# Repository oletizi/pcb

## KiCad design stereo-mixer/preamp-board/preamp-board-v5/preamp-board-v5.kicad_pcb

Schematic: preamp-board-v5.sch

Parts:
C1, C2: 100nF; CP_Radial_D5.0mm_P2.50mm
C3, C4: 47pF; C_Rect_L7.2mm_W2.5mm_P5.00mm_FKS2_FKP2_MKS2_MKP2
J1: Conn_01x20; 20-pin-2.54-edge-connector
R1, R2: 22K; R_Axial_DIN0204_L3.6mm_D1.6mm_P7.62mm_Horizontal
R3, R4: 47K; R_Axial_DIN0204_L3.6mm_D1.6mm_P7.62mm_Horizontal
U1: LM833N; DIP-8_W7.62mm_Socket

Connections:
/+15V: C1.1, J1.16, U1.8 (+VCC)
/-15V: C2.2, J1.20, U1.4 (-VEE)
/L_GAIN_TERM_A: J1.8, R2.2
/L_GAIN_WIPER: C3.2, J1.1, J1.3, J1.5, J1.6, U1.1 (OUT_A)
/L_IN: J1.2, R4.2
/R_GAIN_TERM_A: J1.12, R1.2
/R_GAIN_WIPER: C4.2, J1.9, J1.10, J1.11, J1.13, U1.7 (OUT_B)
/R_IN: J1.4, R3.2
GND: C1.2, C2.1, J1.7, J1.14, J1.18, U1.3 (+INA), U1.5 (+INB)
unnamed: C3.1, R2.1, R4.1, U1.2 (-INA)
unnamed: C4.1, R1.1, R3.1, U1.6 (-INB)

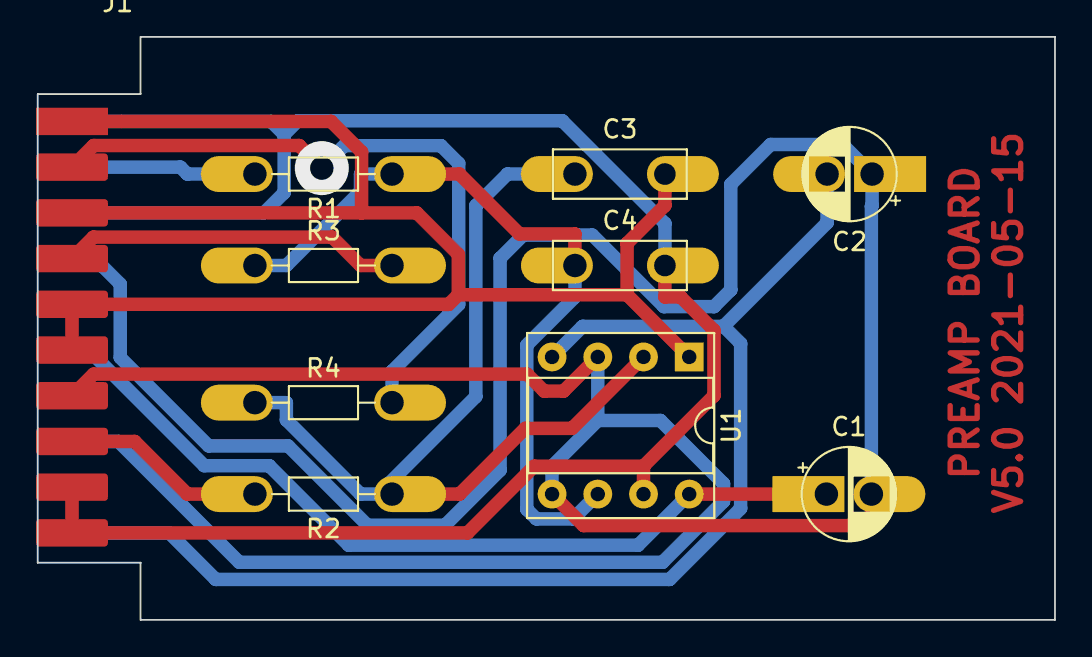
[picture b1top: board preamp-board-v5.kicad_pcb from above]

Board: 2 copper layers, 56.5 x 32.4 mm, 10 parts (0 on the bottom side), 11 nets.

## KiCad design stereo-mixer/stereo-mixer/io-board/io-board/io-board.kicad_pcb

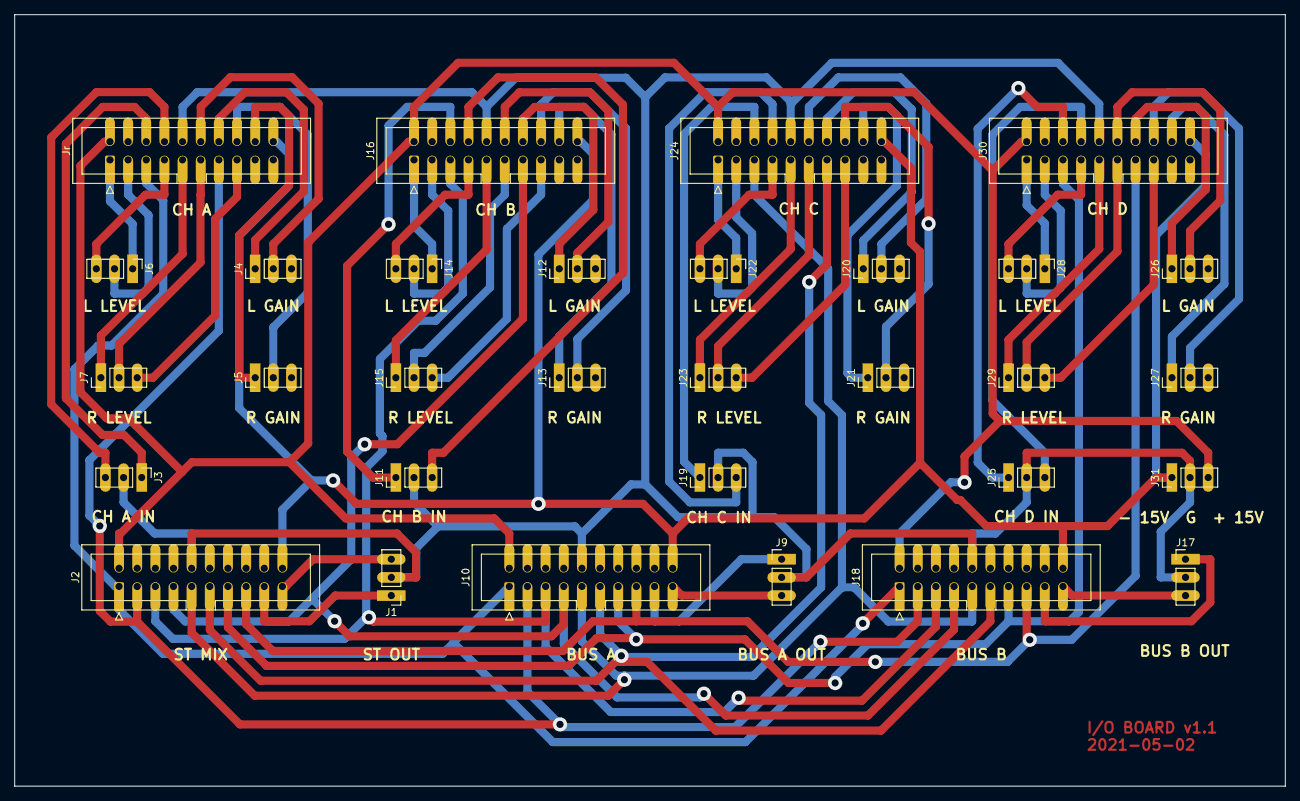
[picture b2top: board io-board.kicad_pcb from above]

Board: 2 copper layers, 177.8 x 108.0 mm, 31 parts (0 on the bottom side), 65 nets.

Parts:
J1: ST OUT; PinHeader_1x03_P2.54mm_Vertical
J2: MIXER BOARD; IDC-Header_2x10_P2.54mm_Vertical
J3: CH A IN: L G R; PinHeader_1x03_P2.54mm_Vertical
J4: CH A L GAIN: TWX; PinHeader_1x03_P2.54mm_Vertical
J5: CH A R GAIN: TWX; PinHeader_1x03_P2.54mm_Vertical
J6: CH A L Level: A W B; PinHeader_1x03_P2.54mm_Vertical
J7: CH A R Level: A W B; PinHeader_1x03_P2.54mm_Vertical
J9: BUS A OUT; PinHeader_1x03_P2.54mm_Vertical
J10: BUS A BOARD; IDC-Header_2x10_P2.54mm_Vertical
J11: CH B IN: L G R; PinHeader_1x03_P2.54mm_Vertical
J12: CH B L GAIN: TWX; PinHeader_1x03_P2.54mm_Vertical
J13: CH B R GAIN: TWX; PinHeader_1x03_P2.54mm_Vertical
J14: CH B L Level: A W B; PinHeader_1x03_P2.54mm_Vertical
J15: CH B R Level: A W B; PinHeader_1x03_P2.54mm_Vertical
J16: CH B PREAMP; IDC-Header_2x10_P2.54mm_Vertical
J17: BUS B OUT; PinHeader_1x03_P2.54mm_Vertical
J18: BUS B BOARD; IDC-Header_2x10_P2.54mm_Vertical
J19: CH C IN: L G R; PinHeader_1x03_P2.54mm_Vertical
J20: CH C L GAIN: TWX; PinHeader_1x03_P2.54mm_Vertical
J21: CH C R GAIN: TWX; PinHeader_1x03_P2.54mm_Vertical
J22: CH C L Level: A W B; PinHeader_1x03_P2.54mm_Vertical
J23: CH C R Level: A W B; PinHeader_1x03_P2.54mm_Vertical
J24: CH C PREAMP; IDC-Header_2x10_P2.54mm_Vertical
J25: CH D IN: L G R; PinHeader_1x03_P2.54mm_Vertical
J26: CH D L GAIN: TWX; PinHeader_1x03_P2.54mm_Vertical
J27: CH D R GAIN: TWX; PinHeader_1x03_P2.54mm_Vertical
J28: CH D L Level: A W B; PinHeader_1x03_P2.54mm_Vertical
J29: CH D R Level: A W B; PinHeader_1x03_P2.54mm_Vertical
J30: CH D PREAMP; IDC-Header_2x10_P2.54mm_Vertical
J31: -15V GND +15V; PinHeader_1x03_P2.54mm_Vertical
Jr: CH A PREAMP; IDC-Header_2x10_P2.54mm_Vertical

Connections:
/+_15V: J2.2, J10.2, J16.2, J18.2, J24.2, J30.2, J31.3, Jr.2
/-_15V: J2.20, J10.20, J16.20, J18.20, J24.20, J30.20, J31.1, Jr.20
/BUS_A_L_OUT: J9.1, J10.17
/BUS_A_R_OUT: J9.3, J10.19
/BUS_B_L_OUT: J17.1, J18.17
/BUS_B_R_OUT: J17.3, J18.19
/CH_A_LEVEL_TERM_B: J6.3, Jr.7
/CH_A_L_GAIN_TERM_A: J4.1, Jr.14
/CH_A_L_GAIN_WIPER: J4.2, Jr.12
/CH_A_L_IN: J3.1, Jr.6
/CH_A_L_LEVEL_TERM_A: J6.1, Jr.1
/CH_A_L_LEVEL_WIPER: J6.2, Jr.3
/CH_A_L_OUT: J2.1, J10.1, J18.1, Jr.5
/CH_A_R_GAIN_TERM_A: J5.1, Jr.18
/CH_A_R_GAIN_WIPER: J5.2, Jr.16
/CH_A_R_IN: J3.3, Jr.8
/CH_A_R_LEVEL_TERM_A: J7.1, Jr.9
/CH_A_R_LEVEL_TERM_B: J7.3, Jr.15
/CH_A_R_LEVEL_WIPER: J7.2, Jr.11
/CH_A_R_OUT: J2.3, J10.3, J18.3, Jr.13
/CH_B_LEVEL_TERM_B: J14.3, J16.7
/CH_B_L_GAIN_TERM_A: J12.1, J16.14
/CH_B_L_GAIN_WIPER: J12.2, J16.12
/CH_B_L_IN: J11.1, J16.6
/CH_B_L_LEVEL_TERM_A: J14.1, J16.1
/CH_B_L_LEVEL_WIPER: J14.2, J16.3
/CH_B_L_OUT: J2.5, J10.5, J16.5, J18.5
/CH_B_R_GAIN_TERM_A: J13.1, J16.18
/CH_B_R_GAIN_WIPER: J13.2, J16.16
/CH_B_R_IN: J11.3, J16.8
/CH_B_R_LEVEL_TERM_A: J15.1, J16.9
/CH_B_R_LEVEL_TERM_B: J15.3, J16.15
/CH_B_R_LEVEL_WIPER: J15.2, J16.11
/CH_B_R_OUT: J2.7, J10.7, J16.13, J18.7
/CH_C_LEVEL_TERM_B: J22.3, J24.7
/CH_C_L_GAIN_TERM_A: J20.1, J24.14
/CH_C_L_GAIN_WIPER: J20.2, J24.12
/CH_C_L_IN: J19.1, J24.6
/CH_C_L_LEVEL_TERM_A: J22.1, J24.1
/CH_C_L_LEVEL_WIPER: J22.2, J24.3
/CH_C_L_OUT: J2.9, J10.9, J18.9, J24.5
/CH_C_R_GAIN_TERM_A: J21.1, J24.18
/CH_C_R_GAIN_WIPER: J21.2, J24.16
/CH_C_R_IN: J19.3, J24.8
/CH_C_R_LEVEL_TERM_A: J23.1, J24.9
/CH_C_R_LEVEL_TERM_B: J23.3, J24.15
/CH_C_R_LEVEL_WIPER: J23.2, J24.11
/CH_C_R_OUT: J2.11, J10.11, J18.11, J24.13
/CH_D_LEVEL_TERM_B: J28.3, J30.7
/CH_D_L_GAIN_TERM_A: J26.1, J30.14
/CH_D_L_GAIN_WIPER: J26.2, J30.12
/CH_D_L_IN: J25.1, J30.6
/CH_D_L_LEVEL_TERM_A: J28.1, J30.1
/CH_D_L_LEVEL_WIPER: J28.2, J30.3
/CH_D_L_OUT: J2.13, J10.13, J18.13, J30.5
/CH_D_R_GAIN_TERM_A: J27.1, J30.18
/CH_D_R_GAIN_WIPER: J27.2, J30.16
/CH_D_R_IN: J25.3, J30.8
/CH_D_R_LEVEL_TERM_A: J29.1, J30.9
/CH_D_R_LEVEL_TERM_B: J29.3, J30.15
/CH_D_R_LEVEL_WIPER: J29.2, J30.11
/CH_D_R_OUT: J2.15, J10.15, J18.15, J30.13
/ST_L_OUT: J1.1, J2.17
/ST_R_OUT: J1.3, J2.19
GND: J1.2, J2.10, J3.2, J9.2, J10.10, J11.2, J16.10, J17.2, J18.10, J19.2, J24.10, J25.2, J30.10, J31.2, Jr.10

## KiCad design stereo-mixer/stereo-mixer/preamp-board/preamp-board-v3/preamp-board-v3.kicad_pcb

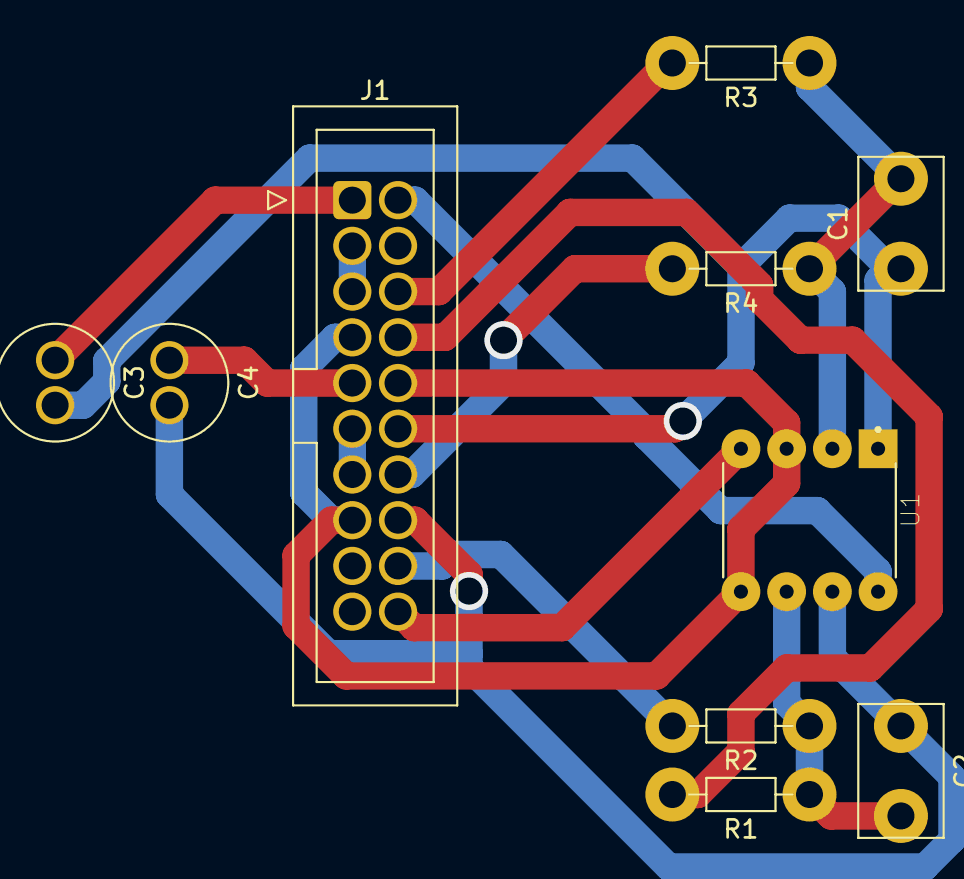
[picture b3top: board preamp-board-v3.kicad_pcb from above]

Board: 2 copper layers, 10 parts (0 on the bottom side), 15 nets.

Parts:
C1, C2: 47pF; C_Rect_L7.2mm_W4.5mm_P5.00mm_FKS2_FKP2_MKS2_MKP2
C3, C4: 100uF; C_Radial_D6.3mm_H11.0mm_P2.50mm
J1: I/O; IDC-Header_2x10_P2.54mm_Vertical
R1, R3: 47K; R_Axial_DIN0204_L3.6mm_D1.6mm_P7.62mm_Horizontal
R2, R4: 22K; R_Axial_DIN0204_L3.6mm_D1.6mm_P7.62mm_Horizontal
U1: LM833N; DIP794W45P254L959H508Q8

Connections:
GND: J1.7, J1.10, J1.15, U1.3, U1.5
unnamed: C1.1, C3.2, J1.12, U1.1
unnamed: C1.2, R3.1, R4.1, U1.2
unnamed: C2.1, C4.2, J1.16, U1.7
unnamed: C2.2, R1.1, R2.1, U1.6
unnamed: C3.1, J1.1
unnamed: C4.1, J1.9
unnamed: J1.2, U1.8
unnamed: J1.3, J1.5
unnamed: J1.6, R3.2
unnamed: J1.8, R1.2
unnamed: J1.11, J1.13
unnamed: J1.14, R4.2
unnamed: J1.18, R2.2
unnamed: J1.20, U1.4

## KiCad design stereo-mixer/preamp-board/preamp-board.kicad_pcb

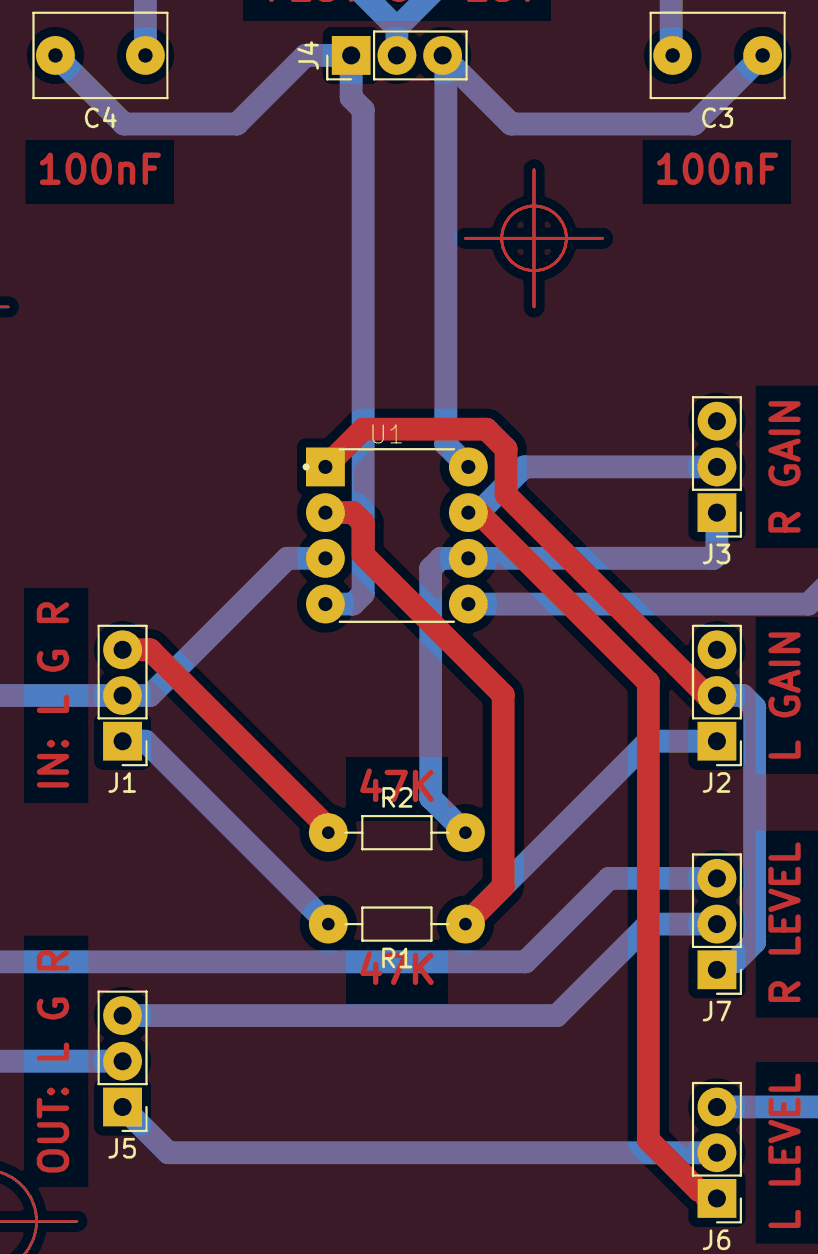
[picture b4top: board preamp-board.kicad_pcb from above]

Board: 2 copper layers, 12 parts (0 on the bottom side), 11 nets.

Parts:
C3, C4: 100nF; C_Rect_L7.2mm_W4.5mm_P5.00mm_FKS2_FKP2_MKS2_MKP2
J1: IN: L G R; PinHeader_1x03_P2.54mm_Vertical
J2: L GAIN POT; PinHeader_1x03_P2.54mm_Vertical
J3: R GAIN POT; PinHeader_1x03_P2.54mm_Vertical
J4: PWR: +15 G -15; PinHeader_1x03_P2.54mm_Vertical
J5: OUT: L G R; PinHeader_1x03_P2.54mm_Vertical
J6: L LEVEL POT; PinHeader_1x03_P2.54mm_Vertical
J7: R LEVEL POT; PinHeader_1x03_P2.54mm_Vertical
R1, R2: 47K; R_Axial_DIN0204_L3.6mm_D1.6mm_P7.62mm_Horizontal
U1: LM833N; DIP794W45P254L959H508Q8

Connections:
GND: C3.2, C4.1, J1.2, J4.2, J5.2, J6.3, J7.3, U1.3, U1.5
unnamed: C3.1, J4.3, U1.8
unnamed: C4.2, J4.1, U1.4
unnamed: J1.1, R1.2
unnamed: J1.3, R2.1
unnamed: J2.1, R1.1, U1.2
unnamed: J2.2, J7.1, U1.1
unnamed: J3.1, R2.2, U1.6
unnamed: J3.2, J6.1, U1.7
unnamed: J5.1, J6.2
unnamed: J5.3, J7.2

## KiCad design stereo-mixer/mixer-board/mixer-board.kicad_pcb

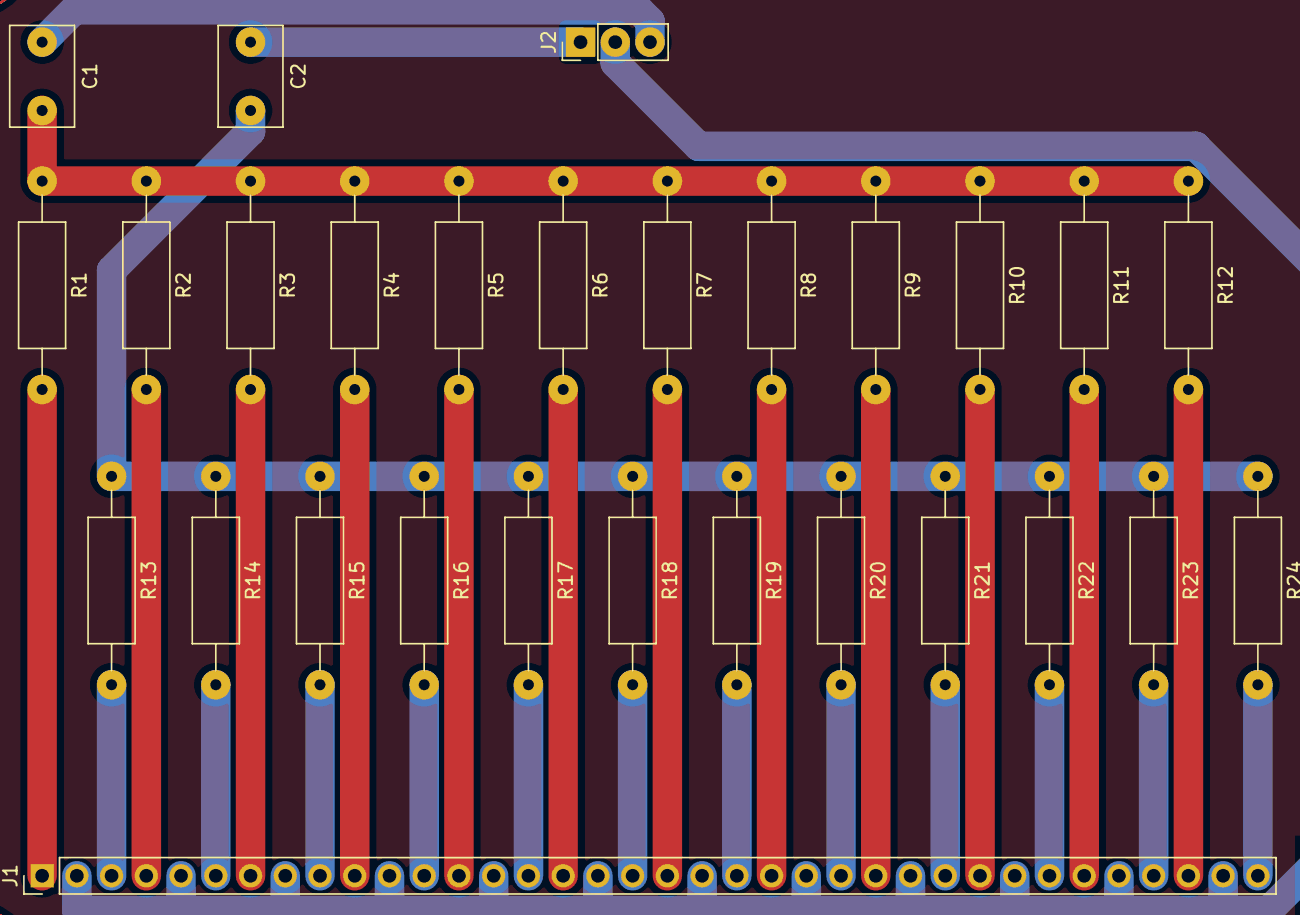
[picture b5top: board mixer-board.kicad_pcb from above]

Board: 2 copper layers, 28 parts (0 on the bottom side), 29 nets.

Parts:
C1, C2: 10uF; C_Rect_L7.2mm_W4.5mm_P5.00mm_FKS2_FKP2_MKS2_MKP2
J1: Conn_01x36_Male; PinHeader_1x36_P2.54mm_Vertical
J2: Conn_01x03_Male; PinHeader_1x03_P2.54mm_Vertical
R1, R2, R3, R4, R5, R6, R7, R8, R9, R10, R11, R12, R13, R14, R15, R16, R17, R18, R19, R20, R21, R22, R23, R24: 22K; R_Axial_DIN0309_L9.0mm_D3.2mm_P15.24mm_Horizontal

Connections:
GND: J1.2, J1.5, J1.8, J1.11, J1.14, J1.17, J1.20, J1.23, J1.26, J1.29, J1.32, J1.35, J2.2
unnamed: C1.1, J2.3
unnamed: C1.2, R1.1, R2.1, R3.1, R4.1, R5.1, R6.1, R7.1, R8.1, R9.1, R10.1, R11.1, R12.1
unnamed: C2.1, J2.1
unnamed: C2.2, R13.1, R14.1, R15.1, R16.1, R17.1, R18.1, R19.1, R20.1, R21.1, R22.1, R23.1, R24.1
unnamed: J1.1, R1.2
unnamed: J1.3, R13.2
unnamed: J1.4, R2.2
unnamed: J1.6, R14.2
unnamed: J1.7, R3.2
unnamed: J1.9, R15.2
unnamed: J1.10, R4.2
unnamed: J1.12, R16.2
unnamed: J1.13, R5.2
unnamed: J1.15, R17.2
unnamed: J1.16, R6.2
unnamed: J1.18, R18.2
unnamed: J1.19, R7.2
unnamed: J1.21, R19.2
unnamed: J1.22, R8.2
unnamed: J1.24, R20.2
unnamed: J1.25, R9.2
unnamed: J1.27, R21.2
unnamed: J1.28, R10.2
unnamed: J1.30, R22.2
unnamed: J1.31, R11.2
unnamed: J1.33, R23.2
unnamed: J1.34, R12.2
unnamed: J1.36, R24.2

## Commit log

2021-04-11 init
2021-04-13 moved some stuff around
2021-04-13 version 2; removed all unnecessary components; consolidated print onto a single page
2021-04-16 added coupling caps to mixer board
2021-04-21 preamp board v3 w/ 20-pin connector
2021-04-21 moved stuff
2021-04-21 moved more stuff
2021-04-23 initial io-board w/ labels
2021-04-23 updated CH_B_ labels
2021-04-23 added mixer I/O and started bus I/O
2021-04-24 autorouted the I/O board
2021-04-24 minor adjustment to I/O board layout to avoid board edge
2021-04-24 added labels and fill areas to I/O board
2021-04-25 updated after print and etch
2021-05-01 cnc stuff
2021-05-01 more cnc stuff; sorted out alignment holes
2021-05-02 updated for cnc
2021-05-02 added stray grbl and flatcam files.
2021-05-02 testing autoleveler
2021-05-03 mostly-successful cnc engraving run
2021-05-03 directory structure cleanup]
2021-05-03 moved Flatcam assets for engraving to the engraving subfolder to make room for parallel "milling" assets"
2021-05-03 added exelon file for alignment holes
2021-05-04 added alignment holes nc file
2021-05-04 io-board milling
2021-05-05 cleanup
2021-05-06 milling g-code for v4 of preamp board
2021-05-06 first milling pass
2021-05-07 pcb2cgode stuff
2021-05-07 stubbed out simplified CLI around pcb2gcode
2021-05-07 nc files for preamp board seem ok
2021-05-08 tinkering with a purpose-built CLI wrapper for pcb2gcode; added a 3d model fixture for holding pcbs in cnc
2021-05-08 added a pcb layout specific to milling
2021-05-08 removed stale excellon and g-code files
2021-05-08 removed stale drilling file
2021-05-08 removed io-board milling b/c its borken
2021-05-08 I mean it this time.
2021-05-08 io-board cleanup
2021-05-08 more cleanup
2021-05-08 removed top-level pcbnew file
2021-05-08 removed top-level schematic
2021-05-08 generated g-code for mixed engraving and milling process
2021-05-08 mods to alignment-hole script
2021-05-09 fine-tuning io-board mixed mill/drill/engrave
2021-05-09 more fine-tuning optimal depth for engraving to avoid gaps.
2021-05-09 more engraving depth fine tuning (Z-0.2). Added procedure and settings notes
2021-05-12 updated g-code and excellon
2021-05-12 added edge cuts gerber file
2021-05-12 updated notes for io-board mixed
2021-05-12 remove old preamp board files
2021-05-12 remove more old preamp board files
2021-05-12 added top-level notes
2021-05-15 edge connector preamp board
2021-05-16 pcb2gcode
2021-05-21 fusion 360 gcode for preamp board
